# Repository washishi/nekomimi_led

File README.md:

# Nekomimi LED  
M5StackのGO BOTTOM等に直接取り付けれるオリジナルのネコミミ型LED基板です  
NeoPixel(WS2812)互換のRGB LEDが左右に9個ずつ合計18個付いており独立して色や明るさ等を制御することができます  

※完成品 や 組立キット、オプション外装等を[Booth](https://washishi.booth.pm/)で頒布もしています
# 回路図、作り方
  回路図、作り方等の詳細については[こちら](schematics/docs/README.md)へ  
  オプション外装の利用方法については[こちら](case/README.md)へ
  <br>

# 使い方
主に下記に直接取り付けることができます  
- <a href="https://docs.m5stack.com/ja/base/m5go_bottom" target="_blank" rel="noopener noreferrer">M5GO BOTTOM</a> BASIC用 (M5GO,FIREは標準添付)   
- <a href="https://docs.m5stack.com/ja/base/m5go_bottom2" target="_blank" rel="noopener noreferrer">M5GO BOTTOM2</a> CORE2用 (CORE2 for AWS は標準添付)
- <a href="https://docs.m5stack.com/ja/module/M5GO3%20Bottom" target="_blank" rel="noopener noreferrer">M5GO3 BOTTOM</a> CoreS3用 (DINベースにそのままつけた場合はコネクタ位置が異なるため左寄りになります)
  
取り付け例  

なおM5Stick系やM5Atom系、M5DialやM5NanoC6などもGROVEポートがあれば基本的に利用可能です  
物理的に干渉する場合はGROVEケーブルとGROVEコネクタを使えば[延長して取り付ける](docs/images/cable_connect.png)こともできます   
<br>  

また[オプション外装](case)を利用してはんだ付けを含む工作を行う場合は下記に取り付け可能となります
  - 直接取り付けできる前記のGO BOTTOM系全て
  - <a href="https://docs.m5stack.com/ja/base/DIN%20BASE" target="_blank" rel="noopener noreferrer">DIN BASE</a> (CoreS3に標準添付)  
  - ししかわさん版(アールティVer. α版,β版)ｽﾀｯｸﾁｬﾝ (V0.2.1基板にPH-4Pコネクタ実装済の物)  

<br>
オプション外装を利用した取り付け例  

&emsp;左から DIN BASE基板ｽﾀｯｸﾁｬﾝ、ししかわさん版ｽﾀｯｸﾁｬﾝ、GO BOTTOM2基板ｽﾀｯｸﾁｬﾝ  

# 使用するGPIO
GO_BOTTOM系やDIN BASEへの接続 または ｽﾀｯｸﾁｬﾝ基板 V0.2.1 の場合は  
PortBのOUTPUT(O)端子を利用してGPIO番号は下記となります  
|Core|利用するGPIO|  
|:--|:-:|  
|BASIC/GRAY/M5GO/FIRE|26|  
|CORE2/CORE2 for AWS|26|  
|CoreS3|9|  

# ソフトウエアでの利用について
Arduino IDE や VSCode + PlatformIO で利用する場合は
[FastLED](https://github.com/FastLED/FastLED)や[Adafruit NeoPixel](https://github.com/adafruit/Adafruit_NeoPixel)等のライブラリで利用できます  
UIFlowで利用する場合はUnit RGB で LEDの数を 18 として利用できます  
その他に関しては NeoPixel を操作できるライブラリ等があれば利用できると思います

# サンプルプログラム
サンプルプログラムとして [m5stack-avatar-mic-nekomimi_led](https://github.com/washishi/m5stack-avatar-mic-nekomimi_led) を用意しました  
音に合わせてAvatarが口パクしたり、傾いたりすると共にNekomimi LEDが音量に応じて光ります
※Takao Akaki (mongonta0716) さんの [m5stack-avatar-mic](https://github.com/mongonta0716/m5stack-avatar-mic) を改変したものです

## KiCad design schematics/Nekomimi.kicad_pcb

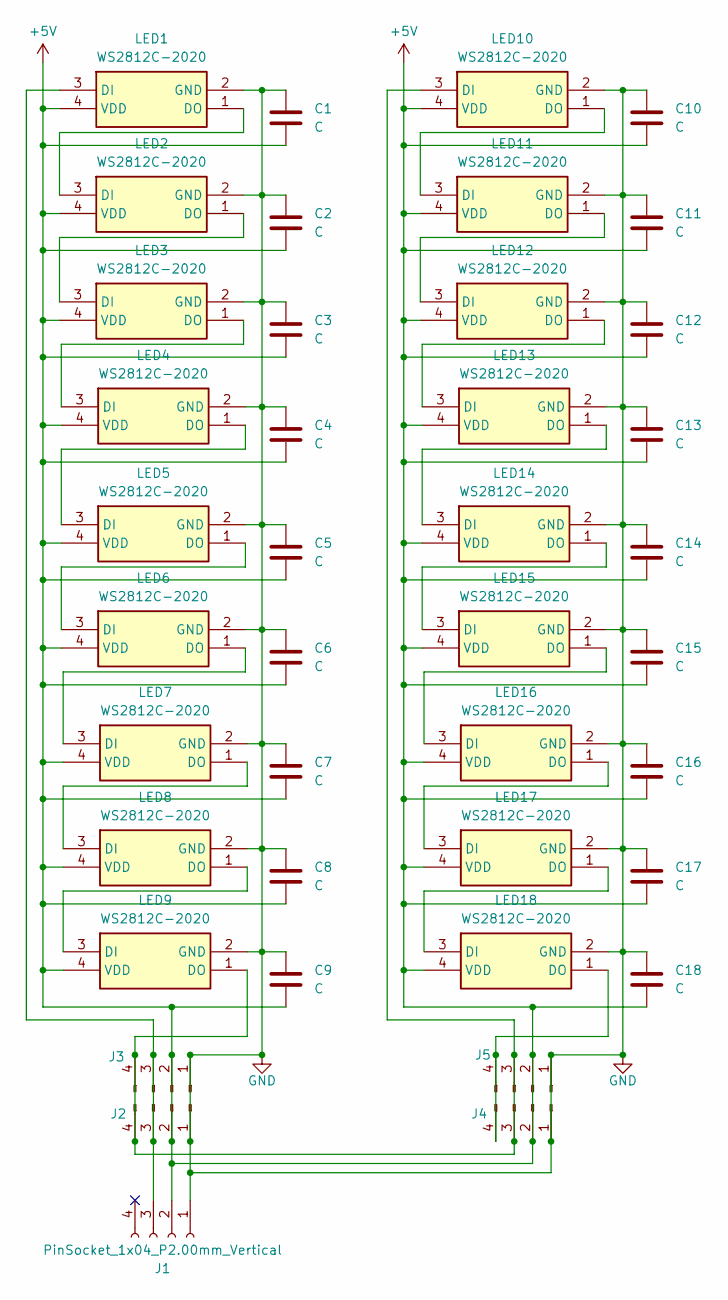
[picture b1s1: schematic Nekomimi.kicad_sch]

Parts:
C1, C2, C3, C4, C5, C6, C7, C8, C9, C10, C11, C12, C13, C14, C15, C16, C17, C18: C; C_0402_1005Metric_Pad0.74x0.62mm_HandSolder; LCSC C1525
J1: PinSocket_1x04_P2.00mm_Vertical
J2, J3, J4, J5: Conn_01x04_Pin; Pad_1x04_P2.00mm
LED1, LED2, LED3, LED4, LED5, LED6, LED7, LED8, LED9, LED10, LED11, LED12, LED13, LED14, LED15, LED16, LED17, LED18: WS2812C-2020; WS2812C2020; Manufacturer_Part_Number WS2812C-2020; LCSC C2976072

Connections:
+5V: C1.2, C2.2, C3.2, C4.2, C5.2, C6.2, C7.2, C8.2, C9.2, C10.2, C11.2, C12.2, C13.2, C14.2, C15.2, C16.2, C17.2, C18.2, J1.2, J2.2, J3.2, J4.2, J5.2, LED1.4 (VDD), LED2.4 (VDD), LED3.4 (VDD), LED4.4 (VDD), LED5.4 (VDD), LED6.4 (VDD), LED7.4 (VDD), LED8.4 (VDD), LED9.4 (VDD), LED10.4 (VDD), LED11.4 (VDD), LED12.4 (VDD), LED13.4 (VDD), LED14.4 (VDD), LED15.4 (VDD), LED16.4 (VDD), LED17.4 (VDD), LED18.4 (VDD)
GND: C1.1, C2.1, C3.1, C4.1, C5.1, C6.1, C7.1, C8.1, C9.1, C10.1, C11.1, C12.1, C13.1, C14.1, C15.1, C16.1, C17.1, C18.1, J1.1, J2.1, J3.1, J4.1, J5.1, LED1.2 (GND), LED2.2 (GND), LED3.2 (GND), LED4.2 (GND), LED5.2 (GND), LED6.2 (GND), LED7.2 (GND), LED8.2 (GND), LED9.2 (GND), LED10.2 (GND), LED11.2 (GND), LED12.2 (GND), LED13.2 (GND), LED14.2 (GND), LED15.2 (GND), LED16.2 (GND), LED17.2 (GND), LED18.2 (GND)
unnamed: J1.3, J2.3, J3.3, LED1.3 (DI)
unnamed: J2.4, J3.4, J4.3, J5.3, LED9.1 (DO), LED10.3 (DI)
unnamed: J4.4, J5.4, LED18.1 (DO)
unnamed: LED1.1 (DO), LED2.3 (DI)
unnamed: LED2.1 (DO), LED3.3 (DI)
unnamed: LED3.1 (DO), LED4.3 (DI)
unnamed: LED4.1 (DO), LED5.3 (DI)
unnamed: LED5.1 (DO), LED6.3 (DI)
unnamed: LED6.1 (DO), LED7.3 (DI)
unnamed: LED7.1 (DO), LED8.3 (DI)
unnamed: LED8.1 (DO), LED9.3 (DI)
unnamed: LED10.1 (DO), LED11.3 (DI)
unnamed: LED11.1 (DO), LED12.3 (DI)
unnamed: LED12.1 (DO), LED13.3 (DI)
unnamed: LED13.1 (DO), LED14.3 (DI)
unnamed: LED14.1 (DO), LED15.3 (DI)
unnamed: LED15.1 (DO), LED16.3 (DI)
unnamed: LED16.1 (DO), LED17.3 (DI)
unnamed: LED17.1 (DO), LED18.3 (DI)

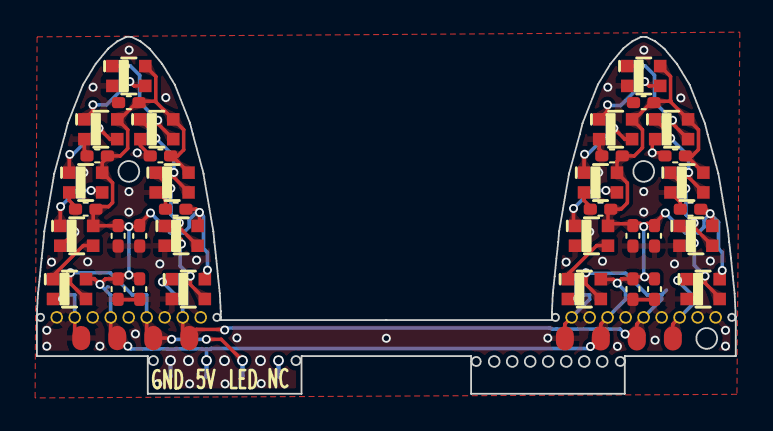
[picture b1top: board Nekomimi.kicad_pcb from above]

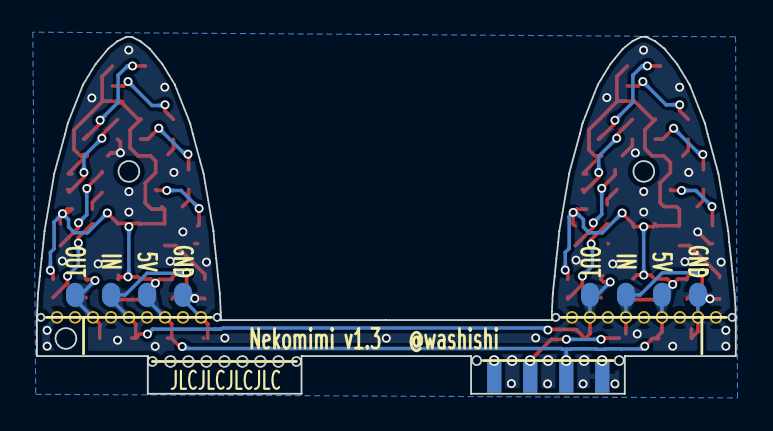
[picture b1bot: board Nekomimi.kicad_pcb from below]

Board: 2 copper layers, 38.8 x 19.8 mm, 47 parts (3 on the bottom side), 21 nets.

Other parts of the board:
hole1, hole2: Hole_1x11 P1.00mm; Hole_1x11_P1.00mm
hole3: Hole_1x9 P1.00mm; Hole_1x9_P1.00mm
tooling hole1, tooling hole2, tooling hole3: Tooling Hole 1.152mm; PCBA_Tooling_Hole

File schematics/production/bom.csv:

Designator,Footprint,Quantity,Value,LCSC Part #
"C1, C10, C11, C12, C13, C14, C15, C16, C17, C18, C2, C3, C4, C5, C6, C7, C8, C9",0402,18,C,C1525
"LED1, LED10, LED11, LED12, LED13, LED14, LED15, LED16, LED17, LED18, LED2, LED3, LED4, LED5, LED6, LED7, LED8, LED9",WS2812C2020,18,WS2812C-2020,C2976072
